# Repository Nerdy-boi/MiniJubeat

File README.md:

# MiniJubeat
Mini controller for Jubeat using MX style switches

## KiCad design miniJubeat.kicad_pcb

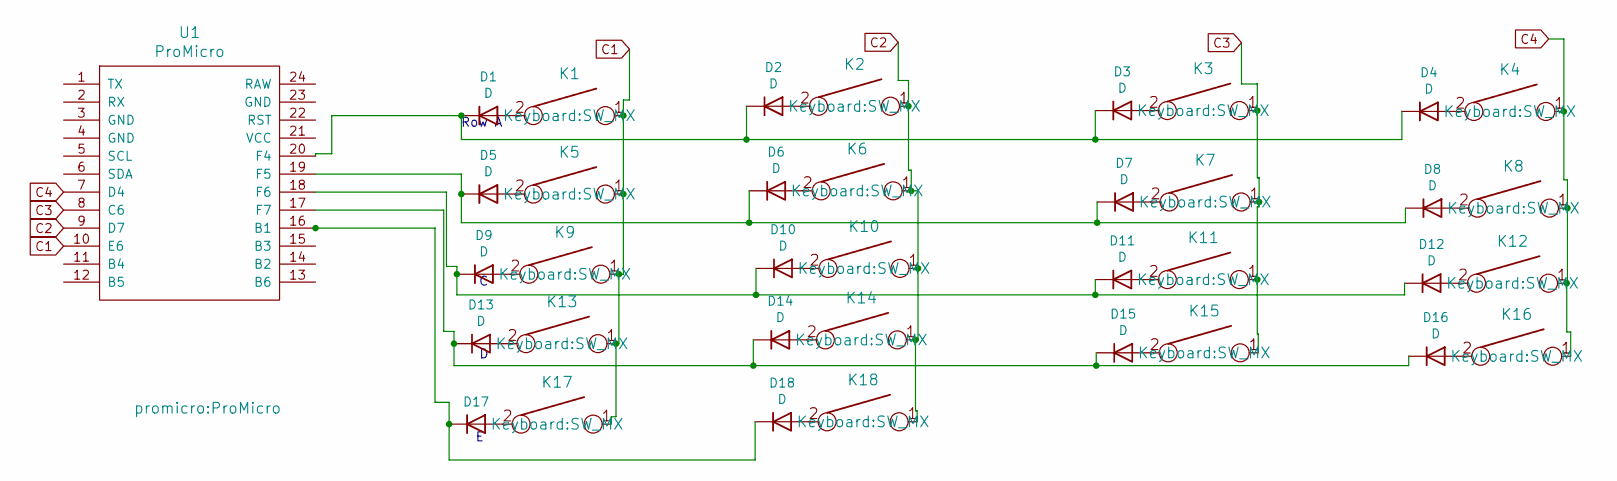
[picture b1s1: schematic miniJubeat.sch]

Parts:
D1, D2, D3, D4, D5, D6, D7, D8, D9, D10, D11, D12, D13, D14, D15, D16, D17, D18: D; D_A-405_P7.62mm_Horizontal
K1, K2, K3, K4, K5, K6, K7, K8, K9, K10, K11, K12, K13, K14, K15, K16, K17, K18: KEYSW; SW_MX
U1: ProMicro

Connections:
C1: K1.1, K5.1, K9.1, K13.1, K17.1, U1.10 (E6)
C2: K2.1, K6.1, K10.1, K14.1, K18.1, U1.9 (D7)
C3: K3.1, K7.1, K11.1, K15.1, U1.8 (C6)
C4: K4.1, K8.1, K12.1, K16.1, U1.7 (D4)
unnamed: D1.1 (K), D2.1 (K), D3.1 (K), D4.1 (K), U1.20 (F4)
unnamed: D1.2 (A), K1.2
unnamed: D2.2 (A), K2.2
unnamed: D3.2 (A), K3.2
unnamed: D4.2 (A), K4.2
unnamed: D5.1 (K), D6.1 (K), D7.1 (K), D8.1 (K), U1.19 (F5)
unnamed: D5.2 (A), K5.2
unnamed: D6.2 (A), K6.2
unnamed: D7.2 (A), K7.2
unnamed: D8.2 (A), K8.2
unnamed: D9.2 (A), K9.2
unnamed: D9.1 (K), D10.1 (K), D11.1 (K), D12.1 (K), U1.18 (F6)
unnamed: D10.2 (A), K10.2
unnamed: D11.2 (A), K11.2
unnamed: D12.2 (A), K12.2
unnamed: D13.1 (K), D14.1 (K), D15.1 (K), D16.1 (K), U1.17 (F7)
unnamed: D13.2 (A), K13.2
unnamed: D14.2 (A), K14.2
unnamed: D15.2 (A), K15.2
unnamed: D16.2 (A), K16.2
unnamed: D17.1 (K), D18.1 (K), U1.16 (B1)
unnamed: D17.2 (A), K17.2
unnamed: D18.2 (A), K18.2

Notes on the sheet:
Row A

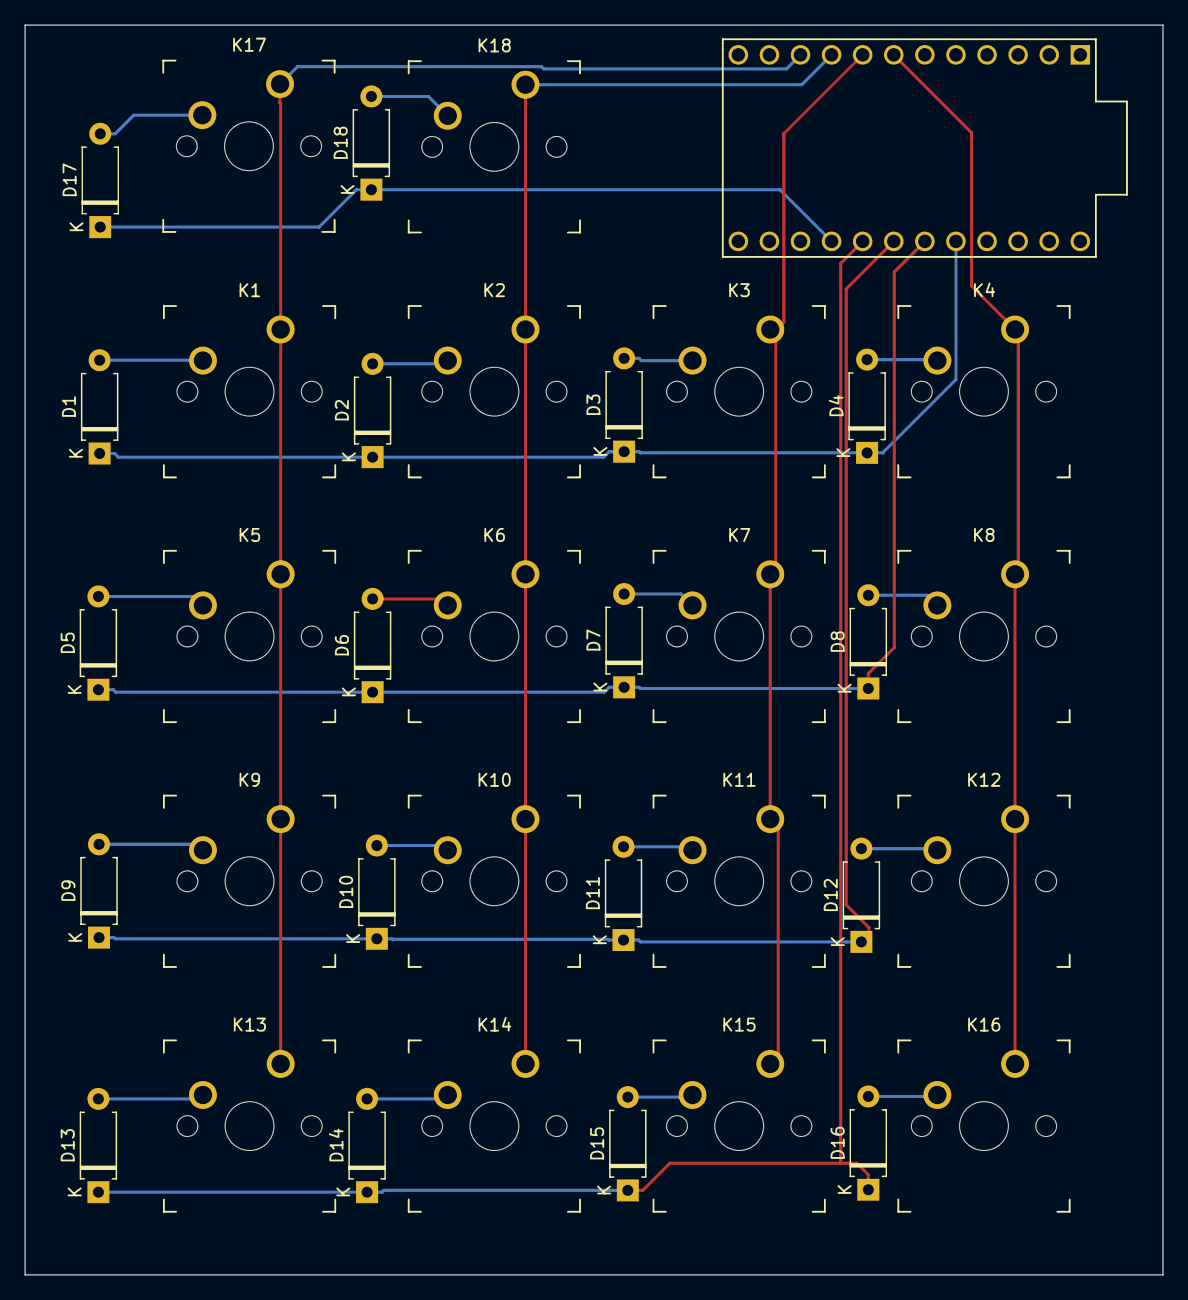
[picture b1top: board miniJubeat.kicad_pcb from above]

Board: 2 copper layers, 93.0 x 102.1 mm, 37 parts (0 on the bottom side), 27 nets.

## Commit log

2020-06-16 Initial Commit of V1
2020-09-27 Added firmware
    Firmware Has options to recognise as a native Keyboard or as a controller so things can be mapped through AHK
